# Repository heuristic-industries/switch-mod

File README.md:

# Switch mod

## What is it?

The "switch mod" retrofits more modern switching functionality to existing pedals that utilize "soft switching" systems based on SPST switches.

Many implementations of these systems lack some features that would be fun to add back in, namely:

### Persistent state between power cycles

One of the only advantages we lose moving away from mechanical switches is the state is no longer independent from the power state.
Many pedals will simply default to being in an "off" state when powered on, which can be problematic for those who have a handful of "always on" effects.
Even worse, some pedals default to being on, forcing users to switch it off at the start of each session.

This mod leverages the microcontroller's onboard EEPROM and will persist the state between settings.

### Hold for momentary operation

A feature becoming more and more popular across many brands, "hold for momentary" allows you to use the pedal as if it had a momentary switch when held down for ~1 second.
It comes in handy when you temporarily want the effect engaged, say, during a solo, without having to hunt for the switch again to turn it off.

## What pedals is it compatible with?

This should work with pedals that use an SPST switch for bypass, and don't already implement features like tap tempo and other hold operations on that switch.
I designed it with Boss dirt pedals in mind, but it can work with many others.

## What does it require?

Installation is simple!

That said, as with any mod there is still a very real risk of ruining a pedal you care about.
I will do my best to explain how to install it, but take no responsibility for anything bad that happens along the way.
You've been warned.

Tools:

- Wire cutters
- Wire strippers
- Soldering iron + solder
- Voltmeter
- A single wire

## Installation

_Pictures coming at some point, sorry._

### 1. Take measurements

Before we start hacking things up, we need to take a few measurements that will impact _how_ we wire the mod up.

First, with the pedal powered on, locate the power jack and determine which leads (or pads, if it's PCB-mounted) are 9V and ground using your voltmeter.
Make a note of these.

Next, locate the pads that the footswitch you want to modify connects to on the board.
Touch the negative lead from your voltmeter to the ground you found on the power jack and the other to each pad on the PCB that the switch connects to.
One will give a positive voltage reading (most likely in the 5 to 9V range) and the other will be ground. Make a note of which is which.

### 2. (maybe) Solder the jumper

If the pedal you're modifying defaults to being "off" when powered on initially, skip this step. If it does power on by default, do the following:

Locate the jumper labeled `J2` on the back side of the mod PCB and place a blob of solder on it, connecting the two pads.

### 3. Sever the switch connections

Grab your wire cutters and cut the leads to the switch at roughly the point where you want the mod PCB to sit inside the enclosure.
Then, strip the ends of the resulting 4 leads. Maybe consider tinning them if they're stranded.

If you're installing this on a more modern pedal that makes use of JST headers, you can skip this and go grab some pre-wired connectors.
So long as the pitch on the connectors is 2.54mm you can solder it onto the mod board and non-destructively connect everything!

### 4. Connect the leads

Start with the leads that go to the switch itself; you can solder those onto the mod board next to the "switch" label.
Polarity doesn't matter, they're both the same as far as we're concerned.

Using the earlier measurements, take the lead connected to the PCB with a positive voltage and hook it into the pad with the `+` sign on the mod board.
The other one will go into the one labeled `-`.

### 5. Connect to power

With the switch spliced into the mod board, we need to power it.
Take some wire and hook it from the 9V terminal on the DC jack to the pad labeled `9V` on the mod board.

### 6. `\m/`

That's it!
Enjoy your freshly-modded pedal.

## Open hardware/software

This repo includes everything you need to build the mod, licensed permissively (see `LICENSE` files in the `firmware` and `pcb` directories).

Hardware hackers can dive right in, but those who don't feel like setting everything up can get pre-built files for PCB fabrication and firmware under [releases](https://github.com/heuristic-industries/switch-mod).

### PCB

The PCB is designed entirely in [KiCad](https://www.kicad.org) and was intended for manufacture through [JLCPCB](https://jlcpcb.com) utilizing their assembly services.
In the release archive you'll find all the files necessary to get the board assembled (with the exception of the `attiny85`, which they don't stock).
You can find all the part numbers in the `LCSC` annotations for each symbol.

If you're making changes and want I highly recommend the wonderful [`kicad-jlcpcb-tools`](https://github.com/Bouni/kicad-jlcpcb-tools) plugin, assuming you want to use JLC for manufacture.

### Firmware

The `README` file in that directory has more information.
Everything is in Rust, because in this house we love modern toolchains and compiler-level safety guarantees.

Boards purchased through me will come pre-flashed, but for those going the DIY route the PCB is designed with a [Tag-Connect header](https://www.tag-connect.com/product/tc2030-idc-nl) to save space (and because it's convenient for me).
It'll work with any AVR programmer; I'm partial to the [SparkFun pocket programmer](https://www.sparkfun.com/products/9825) myself.

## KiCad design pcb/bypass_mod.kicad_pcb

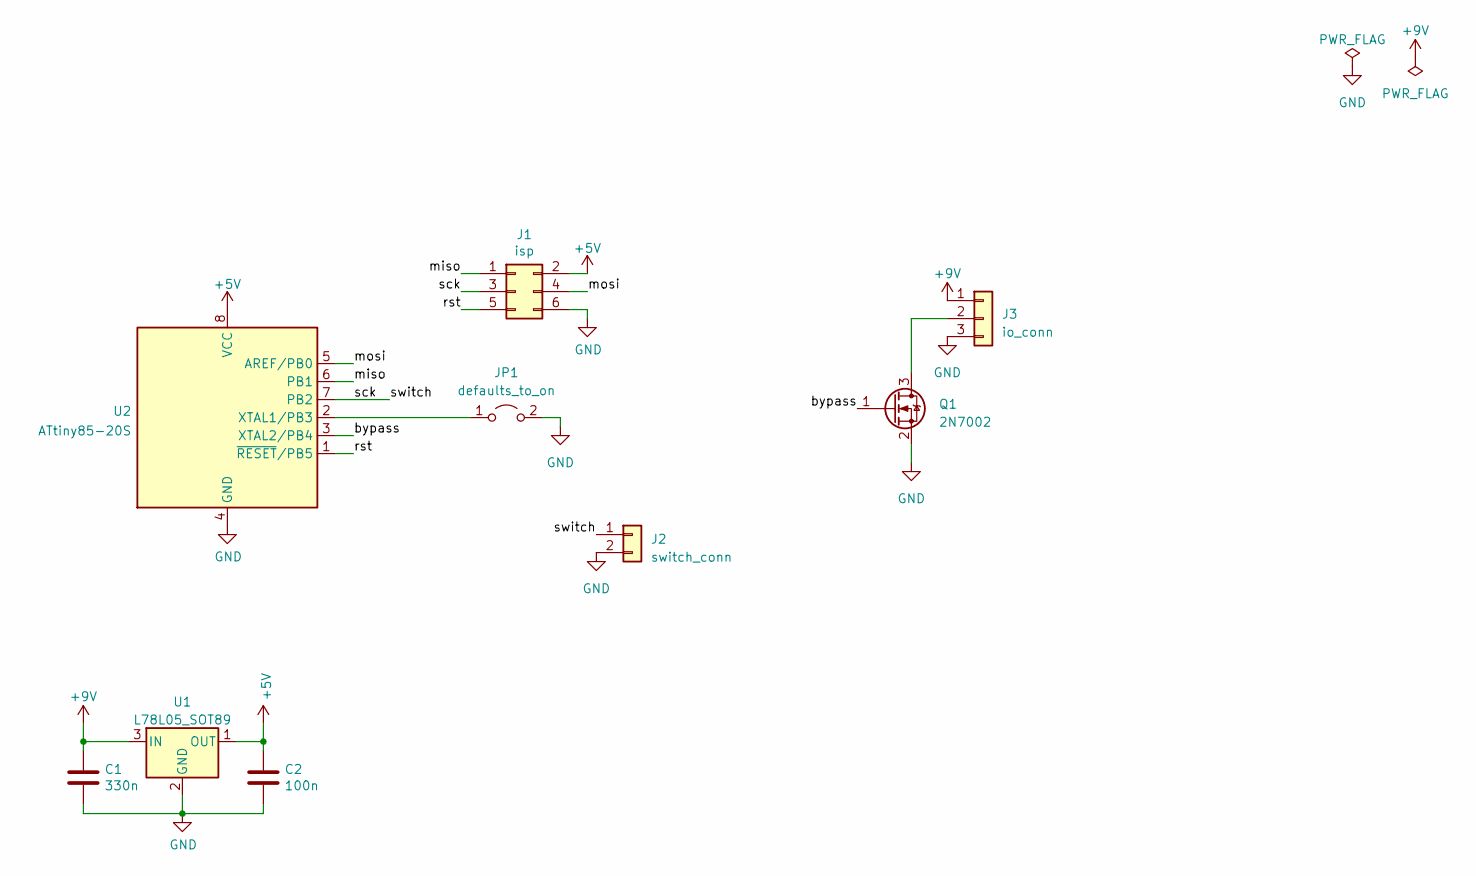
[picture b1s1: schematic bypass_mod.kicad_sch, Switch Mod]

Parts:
C1: 330n; C_0805_2012Metric; LCSC C1740
C2: 100n; C_0805_2012Metric; LCSC C28233
J1: isp; Tag-Connect_TC2030-IDC-NL_2x03_P1.27mm_Vertical
J2: switch_conn; PinHeader_1x02_P2.54mm_Vertical
J3: io_conn; PinHeader_1x03_P2.54mm_Vertical
JP1: defaults_to_on; SolderJumper-2_P1.3mm_Open_TrianglePad1.0x1.5mm
Q1: 2N7002; SOT-23; LCSC C8545
U1: L78L05_SOT89; SOT-89-3; LCSC C71136
U2: ATtiny85-20S; SOICxDIP

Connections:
+5V: C2.1, J1.2, U1.1 (OUT), U2.8 (VCC)
+9V: C1.1, J3.1, U1.3 (IN)
/bypass: Q1.1 (G), U2.3 (XTAL2/PB4)
/miso: J1.1, U2.6 (PB1)
/mosi: J1.4, U2.5 (AREF/PB0)
/rst: J1.5, U2.1 (~RESET/PB5)
/sck: J1.3, J2.1, U2.7 (PB2)
GND: C1.2, C2.2, J1.6, J2.2, J3.3, JP1.2 (B), Q1.2 (S), U1.2 (GND), U2.4 (GND)
unnamed: J3.2, Q1.3 (D)
unnamed: JP1.1 (A), U2.2 (XTAL1/PB3)

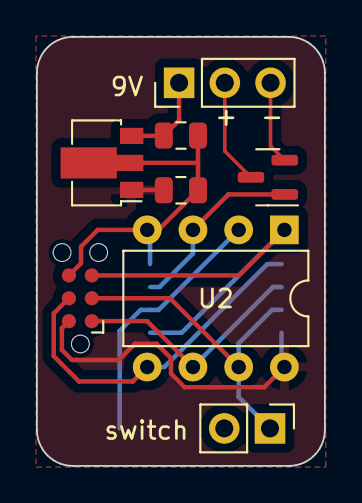
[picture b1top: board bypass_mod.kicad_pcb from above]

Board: 2 copper layers, 16.0 x 23.8 mm, 9 parts (1 on the bottom side), 10 nets.

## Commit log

2023-07-06 first pass
2023-07-20 Add boot delay to fix power sequencing issues
